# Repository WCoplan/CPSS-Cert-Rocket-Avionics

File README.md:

# CPSS-Cert-Rocket-Avionics
Ryan is cool

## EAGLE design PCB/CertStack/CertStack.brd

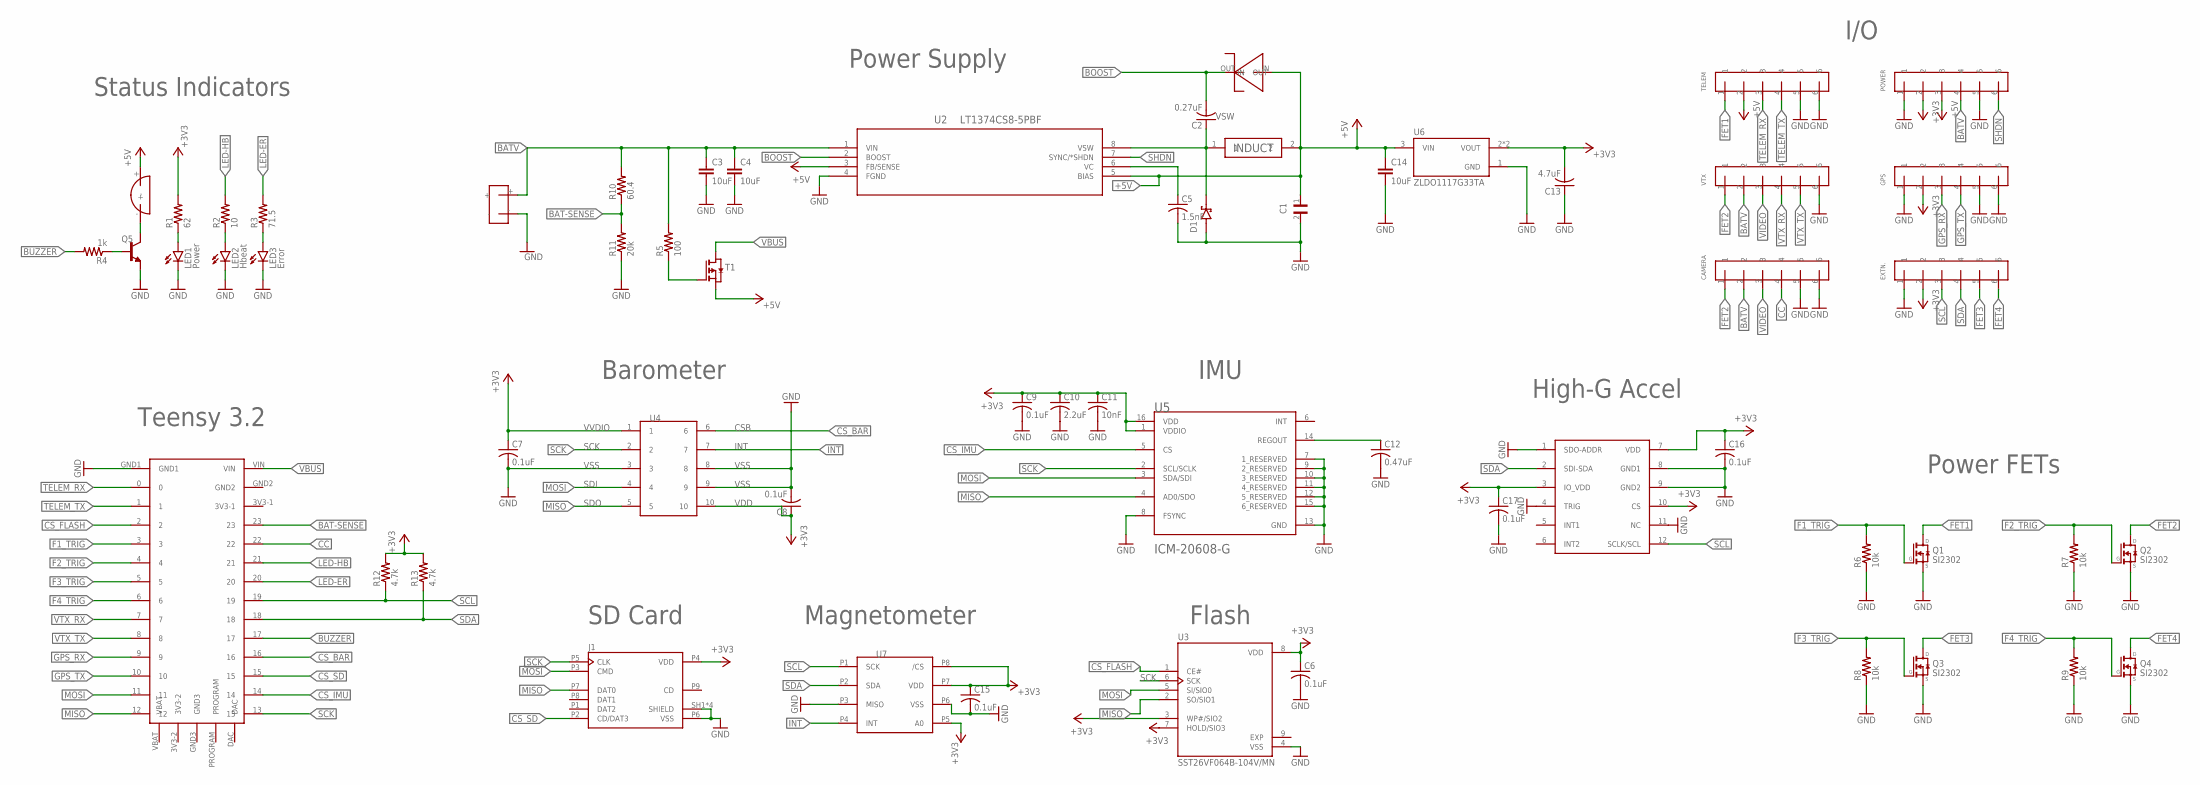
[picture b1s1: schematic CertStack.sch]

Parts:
BATT-CON: PWR-AWG18
C1: T491X106K050AT; CAPMP7343X430N
C2: 0.27uF; C0805
C3, C4, C14: 10uF; 1206
C5: 1.5nF; C0805
C6, C7, C8, C9, C15, C16, C17: 0.1uF; C0805
C10: 2.2uF; C0805
C11: 10nF; C0805
C12: 0.47uF; C0805
C13: 4.7uF; C0805
CAMERA: JST-PH-6
D1: PMEG4020ETP,115; SODFL4725X110N
D2: DO-214AB
EXTN.: JST-PH-6
GPS: JST-PH-6
J1: MEM2075-00-140-01-A; GCT_MEM2075-00-140-01-A
L1: IHLP3232DZER6R8M11
LED1: Power; SML0805
LED2: Hbeat; SML0805
LED3: Error; SML0805
LS1: CMT-8540S
POWER: JST-PH-6
Q1, Q2, Q3, Q4: SI2302; SOT23
Q5: MMBT2222A; SOT23
R1: 62; R0805
R2: 10; R0805
R3: 71.5; R0805
R4: 1k; R0805
R5: 100; R0805
R6, R7, R8, R9: 10k; R0805
R10: 60.4; R0805
R11: 20k; R0805
R12, R13: 4.7k; R0805
T1: DMP3098L-7; SOT-23
TELEM: JST-PH-6
U1: TEENSY-32
U2: LT1374CS8-5PBF; SO-8_S
U3: SST26VF064B-104V/MN; SON127P600X800X80-9N
U4: BMP384; PQFN45P200X200X100-10N
U5: INVENSENSE_ICM-20608-GINVENSENSE_ICM-20608-G_0_0; INVENSENSE_ICM-20608-G_0
U6: ZLDO1117G33TA; SOT230P700X180-4N
U7: MLX90395KDCMLX90395; MLX90395KDC_FPRT
U8: KIONIX_KXTJ3-1057
VTX: JST-PH-6

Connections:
+3V3: C6.1, C7.1, C8.1, C9.1, C10.1, C11.1, C13.2, C15.1, C16.1, C17.1, EXTN..2, GPS.2, J1.P4 (VDD), POWER.2, R1.2, R12.2, R13.2, U3.3 (WP#/SIO2), U3.7 (HOLD/SIO3), U3.8 (VDD), U4.1, U4.10, U5.1 (VDDIO), U5.16 (VDD), U6.2 (VOUT), U6.4 (VOUT), U7.P5 (A0), U7.P7 (VDD), U7.P8 (/CS), U8.3 (IO_VDD), U8.7 (VDD), U8.10 (CS)
+5V: C1.1, C14.1, D2.IN, L1.2, LS1.+, POWER.3, T1.2 (S), TELEM.2, U2.3 (FB/SENSE), U2.5 (BIAS), U6.3 (VIN)
BAT-SENSE: R10.1, R11.2, U1.23
BATV: BATT-CON.+, C3.1, C4.1, CAMERA.2, POWER.4, R5.2, R10.2, U2.1 (VIN), VTX.2
BOOST: C2.2, D2.OUT, U2.2 (BOOST)
BUZZER: R4.2, U1.17
CC: CAMERA.4, U1.22
CS_BAR: U1.16, U4.6
CS_FLASH: U1.2, U3.1 (CE#)
CS_IMU: U1.14, U5.5 (CS)
CS_SD: J1.P2 (CD/DAT3), U1.15
F1_TRIG: Q1.1 (G), R6.2, U1.3
F2_TRIG: Q2.1 (G), R7.2, U1.4
F3_TRIG: Q3.1 (G), R8.2, U1.5
F4_TRIG: Q4.1 (G), R9.2, U1.6
FET1: Q1.3 (D), TELEM.1
FET2: CAMERA.1, Q2.3 (D), VTX.1
FET3: EXTN..5, Q3.3 (D)
FET4: EXTN..6, Q4.3 (D)
GND: BATT-CON.-, C1.2, C3.2, C4.2, C5.2, C6.2, C7.2, C8.2, C9.2, C10.2, C11.2, C12.2, C13.1, C14.2, C15.2, C16.2, C17.2, CAMERA.5, CAMERA.6, D1.2 (A), EXTN..1, GPS.1, GPS.5, GPS.6, J1.P6 (VSS), J1.SH1 (SHIELD), J1.SH2 (SHIELD), J1.SH3 (SHIELD), J1.SH4 (SHIELD), LED1.C, LED2.C, LED3.C, POWER.1, POWER.5, Q1.2 (S), Q2.2 (S), Q3.2 (S), Q4.2 (S), Q5.2 (E), R6.1, R7.1, R8.1, R9.1, R11.1, TELEM.5, TELEM.6, U1.GND1, U2.4 (FGND), U3.4 (VSS), U4.3, U4.8, U4.9, U5.7 (1_RESERVED), U5.8 (FSYNC), U5.9 (2_RESERVED), U5.10 (3_RESERVED), U5.11 (4_RESERVED), U5.12 (5_RESERVED), U5.13 (GND), U5.15 (6_RESERVED), U6.1 (GND), U7.P3 (MISO), U7.P6 (VSS), U8.1 (SDO-ADDR), U8.4 (TRIG), U8.8 (GND1), U8.9 (GND2), U8.11 (NC), VTX.6
GPS_RX: GPS.3, U1.9
GPS_TX: GPS.4, U1.10
INT: U4.7
LED-ER: R3.2, U1.20
LED-HB: R2.2, U1.21
MISO: J1.P7 (DAT0), U1.12, U3.2 (SO/SIO1), U4.5, U5.4 (AD0/SDO)
MOSI: J1.P3 (CMD), U1.11, U3.5 (SI/SIO0), U4.4, U5.3 (SDA/SDI)
unnamed: LED3.A, R3.1
unnamed: C12.1, U5.14 (REGOUT)
unnamed: R5.1, T1.3 (G)
unnamed: LED1.A, R1.1
unnamed: LED2.A, R2.1
unnamed: LS1.-, Q5.3 (C)
unnamed: Q5.1 (B), R4.1
SCK: J1.P5 (CLK), U1.13, U3.6 (SCK), U4.2, U5.2 (SCL/SCLK)
SCL: EXTN..3, R12.1, U1.19, U7.P1 (SCK), U8.12 (SCLK/SCL)
SDA: EXTN..4, R13.1, U1.18, U7.P2 (SDA), U8.2 (SDI-SDA)
SHDN: POWER.6, U2.7 (SYNC/*SHDN)
TELEM_RX: TELEM.3, U1.0
TELEM_TX: TELEM.4, U1.1
VBUS: T1.1 (D), U1.VIN
VC: C5.1, U2.6 (VC)
VIDEO: CAMERA.3, VTX.3
VSW: C2.1, D1.1 (K), L1.1, U2.8 (VSW)
VTX_RX: U1.7, VTX.4
VTX_TX: U1.8, VTX.5

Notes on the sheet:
SD Card
Teensy 3.2
Status Indicators
Power Supply
Barometer
IMU
Flash
I/O
Power FETs
Magnetometer
High-G Accel

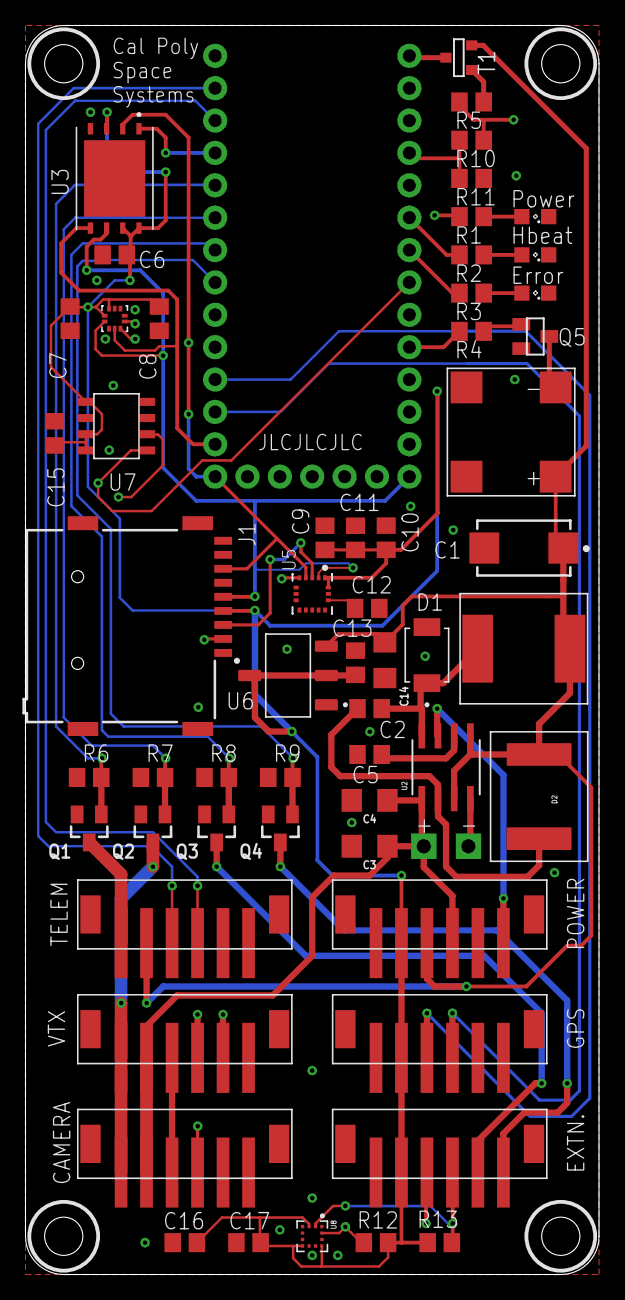
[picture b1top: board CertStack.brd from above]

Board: 4 copper layers, 45.0 x 98.0 mm, 59 parts (0 on the bottom side), 45 nets.

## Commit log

2021-10-23 test push
2021-10-23 testing commits
2021-10-23 test commit
2021-10-23 Add IMU test script 
2021-10-23 Add magnotometer test directory and libraries
2021-10-23 added PCB
2021-10-23 PCB updates
2021-10-29 add gps test script
2021-10-29 Add mag test script
2021-10-29 Add BAR test script and libraries
2021-10-30 add main setup script
2021-10-30 Fix dependency management
2021-11-01 PCB. Big changes.
2021-11-02 linear reg
2021-11-05 Add flash chip test script and library
2021-11-06 add high G accelerometer test script
2021-11-06 PCB:
2021-11-09 move libraries into test script folders
2021-11-16 Added boilerplate test script for Quaternion code
2021-11-17 quat test code
2021-11-20 Final V1 revision of PCB. Just sent off to will to review manufacturing requirements.
2021-11-27 Cleaned up file system
2021-12-04 Cleaned up directory
2022-01-15 Veer's test (do I have permissions?)
2022-01-25 added telemetry arduino code to test scripts and adding GUI folder to ./code
2022-01-25 initialized telemetry react app in Code/GUI
2022-01-29 Changed folder names
2022-01-29 GUI backend update
2022-01-30 Add GUI README
2022-02-01 added widgets
2022-02-01 add flash chip script
2022-02-01 add sd dependency
2022-02-05 Update GUI README
2022-02-08 removed some api call code
2022-02-08 Fixed frontend hooks
2022-02-08 Implemented sockets
2022-02-08 Removed magic numbers
2022-02-09 add reading and writing variable capability to flash chip
2022-02-11 graph max y val now working
2022-02-11 scaling working properly
2022-02-11 formatting graphs, adding commands to modify buffer
2022-02-11 add test for sd card writing
2022-02-12 added AimAssistLogger
2022-02-12 add data logging to flash before sd
2022-02-12 fix terminology
2022-02-12 updating ui and adding telemetry stuff
2022-02-12 fix data logging
2022-02-12 add flash chip fix
2022-02-12 Fixed emission issue, added endconnection command
2022-02-14 Fixed some display errors, updated icon
2022-05-05 fixed error in Telemetry.ino

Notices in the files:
parts and their libraries:
SparkFun-Capacitors: Licensing: Creative Commons ShareAlike 4.0 International - https://creativecommons.org/licenses/by-sa/4.0
